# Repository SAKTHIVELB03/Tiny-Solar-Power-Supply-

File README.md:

# Tiny Solar Power Supply – 3.3V Regulated Output

A compact solar-powered power supply that converts energy from a small solar panel and a single 1.2 V Ni-MH AA rechargeable battery into a stable **3.3 V regulated output**, suitable for low-power embedded and IoT applications.

---

## 📌 Overview

This project demonstrates a **low-power boost converter–based solar supply** using the **AP3015/AP3015A micropower DC/DC step-up converter**.  
During daylight, the solar panel charges the battery and disables the boost converter. When light is no longer available, the circuit automatically enables the boost converter and powers the load from the battery.

The design focuses on **efficiency, simplicity, and compact size**, making it ideal for small standalone electronics.

---

## ⚙️ Features

- Regulated **3.3 V output**
- Operates from a **single 1.2 V Ni-MH AA battery**
- Supports **solar charging**
- Automatic **day/night power switching**
- Low-power, high-efficiency design
- Compact PCB footprint

---

## 🔋 How It Works

1. **Daytime Operation**
   - Solar panel charges the Ni-MH battery through a diode.
   - A MOSFET disables the boost converter to prevent unnecessary power loss.

2. **Nighttime Operation**
   - Solar voltage drops.
   - Boost converter is enabled automatically.
   - Battery voltage is stepped up and regulated to **3.3 V**.

The output voltage is set using a resistor feedback network:

---

## 🧩 Main Components

- **AP3015 / AP3015A** – Micropower boost DC/DC converter  
- **2N7002** – MOSFET for automatic switching  
- **SS14** – Schottky diodes  
- **10 µH Inductor**
- Ceramic capacitors (X7R)

---

## 📋 Bill of Materials (BOM)

| Component | Value / Part Number |
|---------|---------------------|
| IC1 | AP3015 / AP3015A |
| L1 | 10 µH, ≥680 mA |
| D1, D2 | SS14 |
| T1 | 2N7002 |
| R1 | 1 MΩ |
| R2 | 604 kΩ (1%) |
| R3 | 10 kΩ |
| R4 | 1 MΩ |
| C1 | 4.7 µF |
| C2 | 22 µF |
| C3 | 10 pF |

---

## 🔌 Connections

| Connector | Description |
|---------|-------------|
| K1 | 3.3 V Output |
| K2 | Battery Input |
| K3 | Manual ON/OFF (optional) |
| K4 | Solar Panel Input |

---

## 📐 Files Included

- Schematic
- PCB layout
- Gerber files
- BOM
- Documentation

---

## 🛠 Applications

- Solar-powered IoT devices
- Low-power microcontroller projects
- Environmental sensors
- Educational electronics projects

---

## 📄 Reference

Based on **“Tiny Solar Supply – Sunlight In, 3.3 V Out”**  
Original concept by **Clemens Valens**, Elektor Magazine.

---

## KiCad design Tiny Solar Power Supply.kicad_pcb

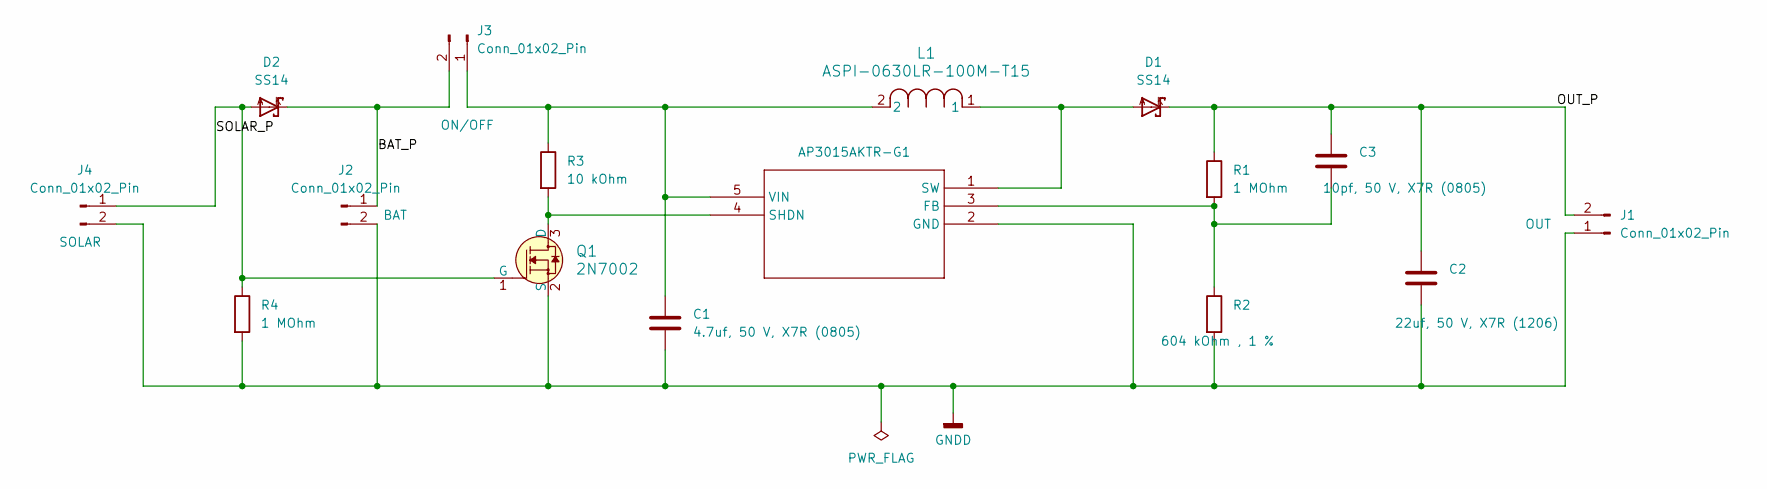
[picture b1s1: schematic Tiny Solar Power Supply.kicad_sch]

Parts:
C1: 4.7uf, 50 V, X7R (0805); C_0805_2012Metric
C2: 22uf, 50 V, X7R (1206); C_1206_3216Metric
C3: 10pf, 50 V, X7R (0805); C_0805_2012Metric
D1, D2: SS14; DO-214AC
J1, J2, J3: Conn_01x02_Pin; PinHeader_1x02_P2.54mm_Vertical
J4: Conn_01x02_Pin; PinHeader_1x02_P2.54mm_Horizontal
L1: ASPI-0630LR-100M-T15; IND_ASPI-0630LR_ABR
Q1: 2N7002; SOT-23-3; MPN 2N7002; Digi-Key_PN 2N7002NCT-ND
R1, R4: 1 MOhm; R_0805_2012Metric
R2: 604 kOhm , 1 %; R_0805_2012Metric
R3: 10 kOhm; R_0805_2012Metric
U1: AP3015AKTR-G1; SOT23-5_1P55X2P9_DIO

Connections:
/BAT_P: D2.K, J2.1, J3.2
/OUT_P: C2.1, C3.1, D1.K, J1.2, R1.1
/SOLAR_P: D2.A, J4.1, Q1.1 (G), R4.1
GNDD: C1.2, C2.2, J1.1, J2.2, J4.2, Q1.2 (S), R2.2, R4.2, U1.2 (GND)
unnamed: C1.1, J3.1, L1.2, R3.1, U1.5 (VIN)
unnamed: Q1.3 (D), R3.2, U1.4 (SHDN)
unnamed: C3.2, R1.2, R2.1, U1.3 (FB)
unnamed: D1.A, L1.1, U1.1 (SW)

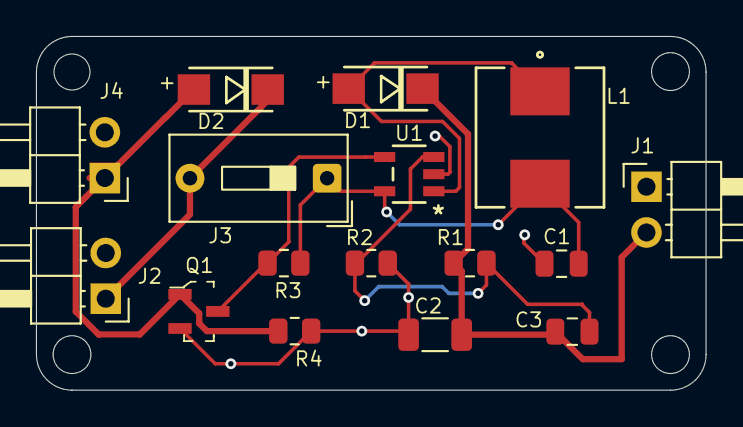
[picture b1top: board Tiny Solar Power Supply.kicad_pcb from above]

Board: 2 copper layers, 37.2 x 19.7 mm, 16 parts (0 on the bottom side), 8 nets.

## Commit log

2026-01-07 Images
2026-01-07 Enhance README with project details and specifications
    Added detailed project overview, key features, circuit functionality, main components, tools used, applications, and project status.
2026-01-07 Update applications list in README
    Removed 'Breadboard power supply' from applications list.
